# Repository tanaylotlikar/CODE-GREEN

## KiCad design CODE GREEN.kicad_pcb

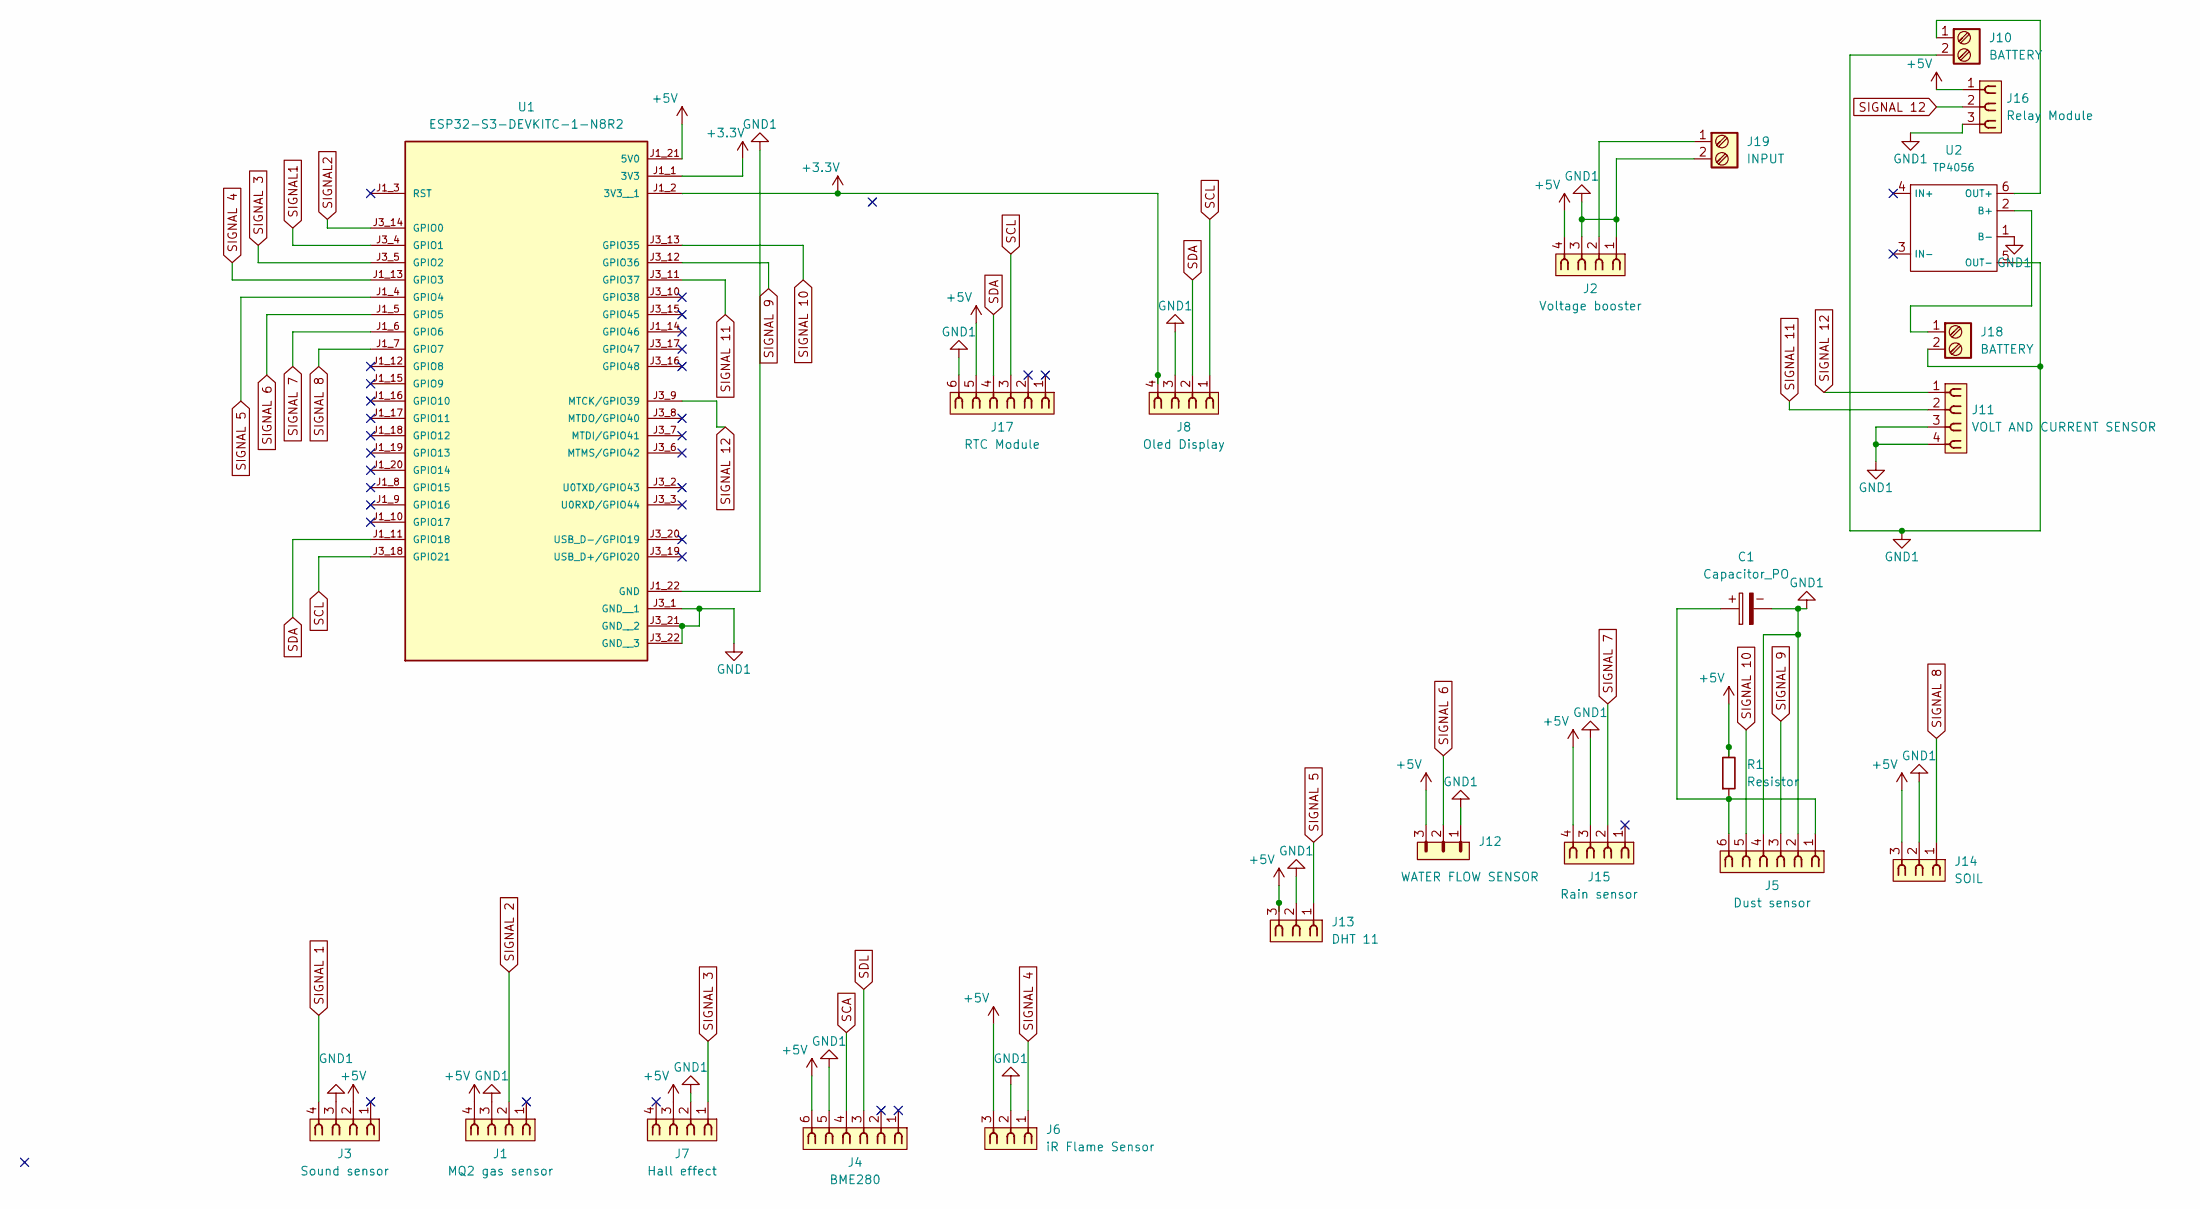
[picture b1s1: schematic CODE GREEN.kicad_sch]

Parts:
C1: Capacitor_PO; CP_Radial_D5.0mm_P2.50mm
J1: MQ2 gas sensor; PinSocket_1x04_P2.54mm_Vertical
J2: Voltage booster; PinSocket_1x04_P2.54mm_Vertical
J3: Sound sensor; PinSocket_1x04_P2.54mm_Vertical
J4: BME280; PinSocket_1x06_P2.54mm_Vertical
J5: Dust sensor; PinSocket_1x06_P2.54mm_Vertical
J6: iR Flame Sensor; PinSocket_1x03_P2.54mm_Vertical
J7: Hall effect; PinSocket_1x04_P2.54mm_Vertical
J8: Oled Display; PinSocket_1x04_P2.54mm_Vertical
J10, J18: BATTERY; TerminalBlock_Phoenix_PT-1,5-2-3.5-H_1x02_P3.50mm_Horizontal
J11: VOLT AND CURRENT SENSOR; PinSocket_1x04_P2.54mm_Vertical
J12: WATER FLOW SENSOR; PinHeader_1x03_P2.54mm_Vertical
J13: DHT 11; PinSocket_1x03_P2.54mm_Vertical
J14: SOIL; PinSocket_1x03_P2.54mm_Vertical
J15: Rain sensor; PinSocket_1x04_P2.54mm_Vertical
J16: Relay Module; PinSocket_1x03_P2.54mm_Vertical
J17: RTC Module; PinSocket_1x06_P2.54mm_Vertical
J19: INPUT; TerminalBlock_Phoenix_PT-1,5-2-3.5-H_1x02_P3.50mm_Horizontal
R1: Resistor; R_Axial_DIN0207_L6.3mm_D2.5mm_P10.16mm_Horizontal
U1: ESP32-S3-DEVKITC-1-N8R2; XCVR_ESP32-S3-DEVKITC-1-N8R2; PARTREV V1
U2: TP4056; TP4056-Module

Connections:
+3.3V: J8.4, U1.J1_1 (3V3), U1.J1_2 (3V3__1)
+5V: J1.4, J2.4, J3.2, J4.6, J6.3, J7.3, J12.3, J13.3, J14.3, J15.4, J16.1, J17.5, R1.2, U1.J1_21 (5V0)
GND1: C1.2, J1.3, J2.1, J2.3, J3.3, J4.5, J5.2, J5.4, J6.2, J7.2, J8.3, J10.2, J11.3, J11.4, J12.1, J13.2, J14.2, J15.3, J16.3, J17.6, J18.2, J19.2, U1.J1_22 (GND), U1.J3_1 (GND__1), U1.J3_21 (GND__2), U1.J3_22 (GND__3), U2.1 (B-), U2.5 (OUT-)
unnamed: C1.1, J5.1, J5.6, R1.1
unnamed: J2.2, J19.1
unnamed: J18.1, U2.2 (B+)
unnamed: J10.1, U2.6 (OUT+)
SCA: J4.4
SCL: J8.1, J17.3, U1.J3_18 (GPIO21)
SDA: J8.2, J17.4, U1.J1_11 (GPIO18)
SDL: J4.3
SIGNAL1: U1.J3_4 (GPIO1)
SIGNAL2: U1.J3_14 (GPIO0)
SIGNAL 1: J3.4
SIGNAL 2: J1.2
SIGNAL 3: J7.1, U1.J3_5 (GPIO2)
SIGNAL 4: J6.1, U1.J1_13 (GPIO3)
SIGNAL 5: J13.1, U1.J1_4 (GPIO4)
SIGNAL 6: J12.2, U1.J1_5 (GPIO5)
SIGNAL 7: J15.2, U1.J1_6 (GPIO6)
SIGNAL 8: J14.1, U1.J1_7 (GPIO7)
SIGNAL 9: J5.3, U1.J3_12 (GPIO36)
SIGNAL 10: J5.5, U1.J3_13 (GPIO35)
SIGNAL 11: J11.2, U1.J3_11 (GPIO37)
SIGNAL 12: J11.1, J16.2, U1.J3_9 (MTCK/GPIO39)

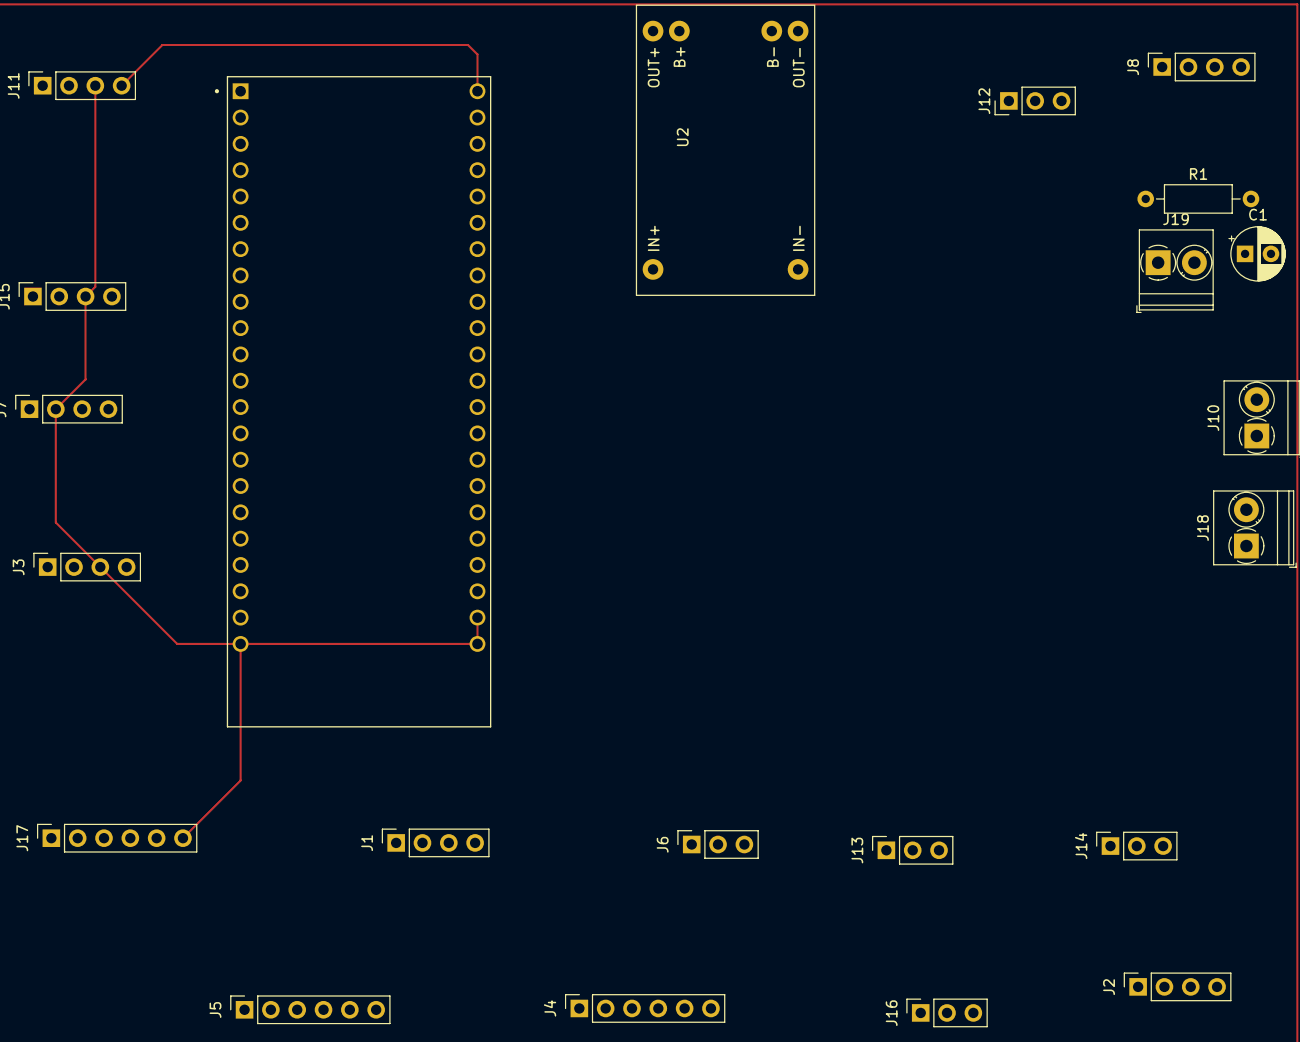
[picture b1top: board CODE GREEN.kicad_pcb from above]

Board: 2 copper layers, 22 parts (0 on the bottom side), 19 nets.

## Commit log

2025-03-18 changes done
